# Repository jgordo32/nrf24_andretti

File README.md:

nrf24_andretti
==============

Firmware project for the wireless controllers on the Andretti Video Game Shirt

When the codebase is a little more mature, either each app or each folder will have it's own more thoroughly explained readme file as the FreeRTOS kernel does.

Authors:
Adam Feinstein
Jonathan Gordon

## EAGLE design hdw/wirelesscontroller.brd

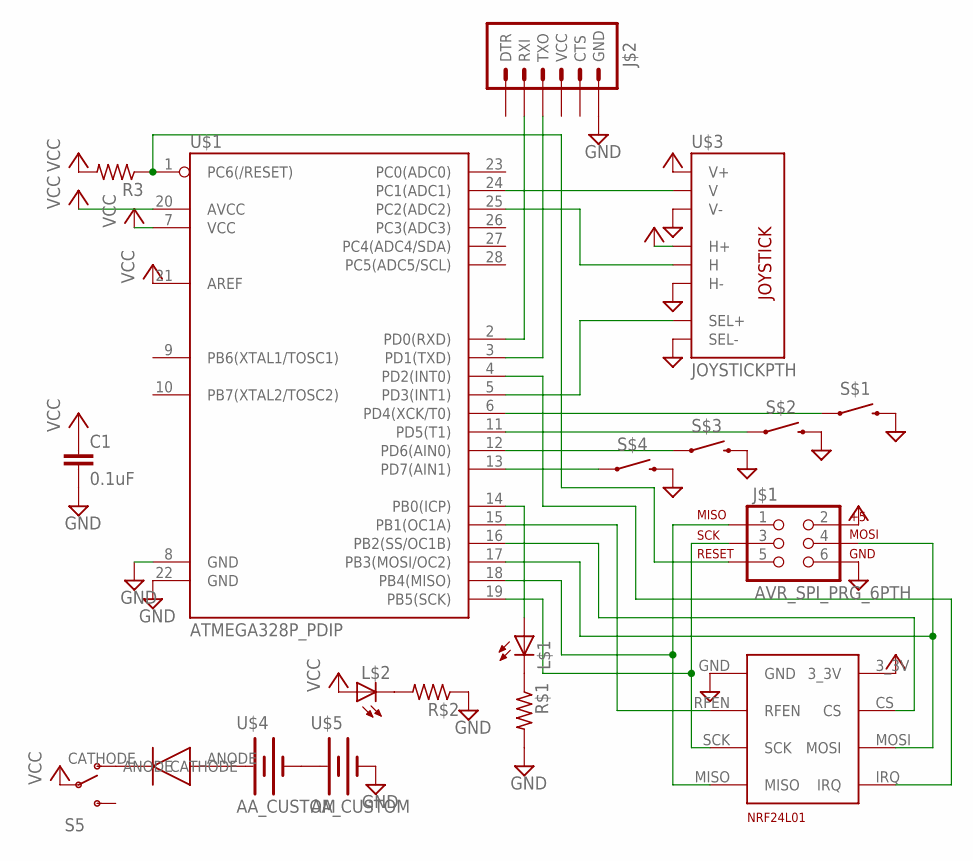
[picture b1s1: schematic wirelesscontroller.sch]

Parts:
C1: 0.1uF; 0603-CAP
D$1: DIODE; R0603
J$1: AVR_SPI_PRG_6PTH; 2X3
J$2: ARDUINO_SERIAL_PROGRAMPTH; 1X06
L$1, L$2: LEDCHIPLED_0603; CHIPLED_0603
R3: R-US_R0603; R0603
R$1, R$2: R-US_R0603; R0603
S5: SWITCH-SPDTPTH; SWITCH-SPDT
S$1, S$2, S$3, S$4: SWITCH-MOMENTARY-212MM; TACTILE-PTH-12MM
U$1: ATMEGA328P_PDIP; DIL28-3
U$2: NRF24L01_BRK; 4X2
U$3: JOYSTICKPTH; JOYSTICK
U$4, U$5: AA_CUSTOM; AACLIP

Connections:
AX: U$1.25 (PC2(ADC2)), U$3.H2 (H)
AY: U$1.24 (PC1(ADC1)), U$3.V2 (V)
B1: S$1.1, U$1.6 (PD4(XCK/T0))
B2: S$2.1, U$1.11 (PD5(T1))
B3: S$3.1, U$1.12 (PD6(AIN0))
B4: S$4.1, U$1.13 (PD7(AIN1))
B5: U$1.5 (PD3(INT1)), U$3.B1A (SEL+)
CS: U$1.16 (PB2(SS/OC1B)), U$2.CS
GND: C1.2, J$1.6, J$2.6 (GND), R$1.2, R$2.1, S$1.3 (2), S$2.3 (2), S$3.3 (2), S$4.3 (2), U$1.8 (GND), U$1.22 (GND), U$2.GND, U$3.B2A (SEL-), U$3.H3 (H-), U$3.V3 (V-), U$5.-
MISO: J$1.1, U$1.18 (PB4(MISO)), U$2.MISO
MOSI: J$1.4, U$1.17 (PB3(MOSI/OC2)), U$2.MOSI
unnamed: D$1.CATHODE, S5.1 (O)
unnamed: U$4.-, U$5.+
unnamed: D$1.ANODE, U$4.+
unnamed: L$2.C, R$2.2
unnamed: L$1.C, R$1.1
unnamed: L$1.A, U$1.14 (PB0(ICP))
RESET: J$1.5, R3.1, U$1.1 (PC6(/RESET))
RFEN: U$1.15 (PB1(OC1A)), U$2.RFEN
RF_IRQ: U$1.4 (PD2(INT0)), U$2.IRQ
RX: J$2.2 (RXI), U$1.2 (PD0(RXD))
SCK: J$1.3, U$1.19 (PB5(SCK)), U$2.SCK
TX: J$2.3 (TXO), U$1.3 (PD1(TXD))
VCC: C1.1, J$1.2, L$2.A, R3.2, S5.2, U$1.7 (VCC), U$1.20 (AVCC), U$1.21 (AREF), U$2.3_3V, U$3.H1 (H+), U$3.V1 (V+)

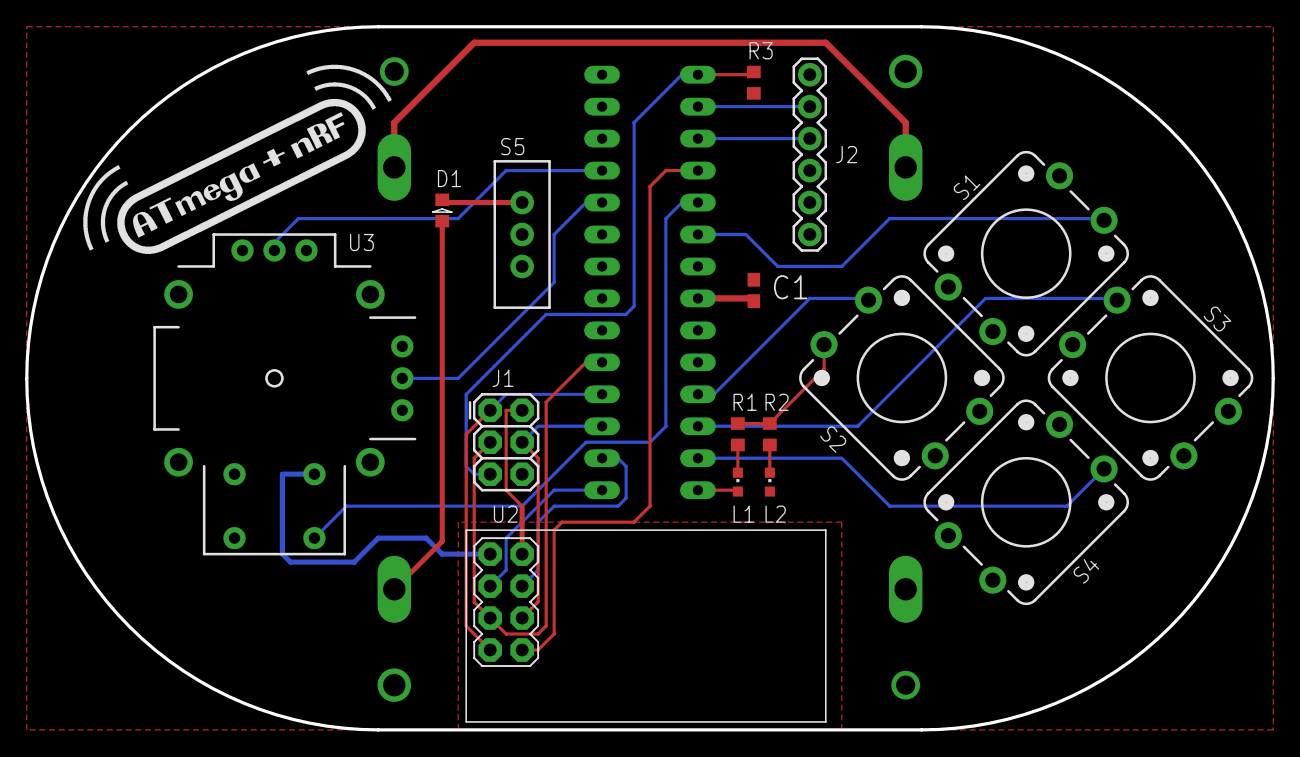
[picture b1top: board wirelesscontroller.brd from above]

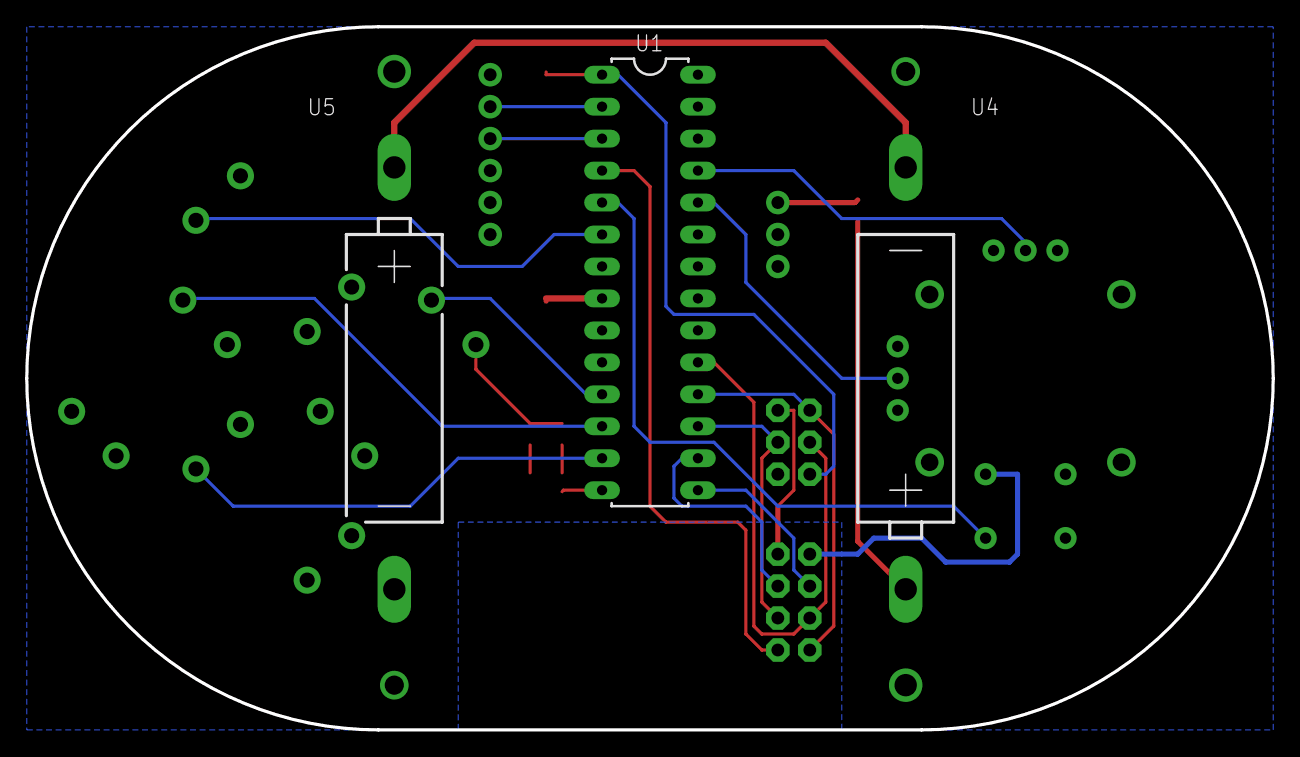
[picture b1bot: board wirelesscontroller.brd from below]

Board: 2 copper layers, 99.1 x 55.9 mm, 19 parts (3 on the bottom side), 24 nets.

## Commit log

2014-03-02 Initializing Repository
    Added first attempt at a .gitignore file and a default .gitattributes
    file
2014-03-02 Adding Arduino, atmega328p, and FreeRTOS filesdhf
    - Updated the .gitignore to ignore dependency files
    - Added the initial Arduino POC code files
    - Added a POC version of the standalone AVR code
    - Added a pretty solid version of the AVR FreeRTOS port for the mega328P
    NOTE: completely untested at this point besides original POC testing
    01/2014
2014-03-02 Created README.md file
2014-03-02 Updating readme
    Tried messing with markdown's paragraph line endings.
2014-03-03 Adding the hardware files
    - Added the Eagle sch and brd files for the wireless controller
2014-03-04 Added bypass cap
    Added a bypass capacitor to the power supply on the controller
2014-05-17 Stable-ish heartbeat on the controller board with radio code seemingly working.
2014-05-17 added game playing sketch
2014-07-14 AutoCAD file for controller case
    File contains the 3D models I made for the PCB, components, buttons,
    switches, and top & bottom plastic pieces.
2014-07-14 Stereolithography files for 3D printing
    .stl files for the plastic components of the case.
2014-07-14 Renderings of controller case
    Renderings for various components of the 3D printed case.

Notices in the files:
parts and their libraries:
SparkFun-DigitalIC: Licensing: CC v3.0 Share-Alike You are welcome to use this library for commercial purposes.
